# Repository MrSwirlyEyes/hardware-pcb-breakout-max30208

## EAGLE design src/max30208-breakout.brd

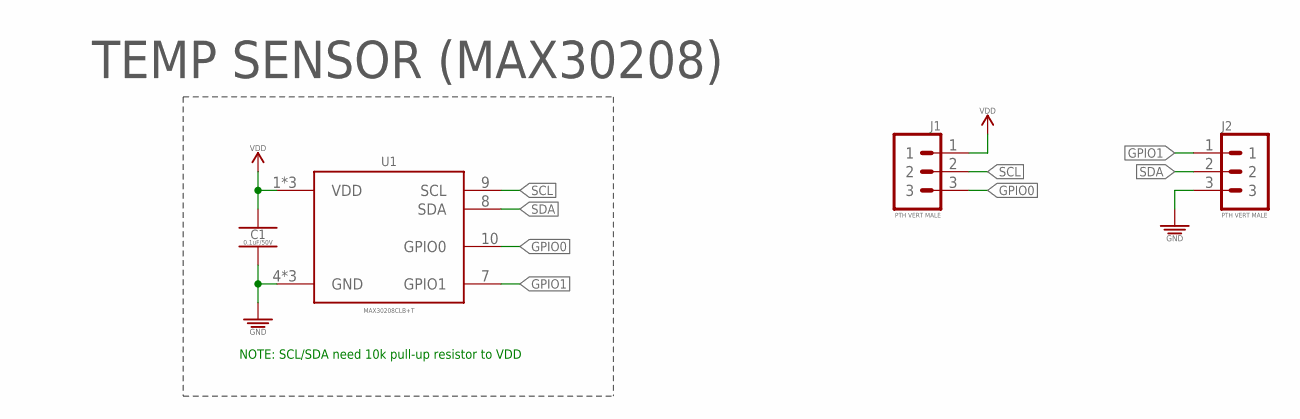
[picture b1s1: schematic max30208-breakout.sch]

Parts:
C1: 0.1uF/50V; CAPC1005X55_SMD-0402
J1, J2: PTH VERT MALE; HDRV3W64P254_1X3_762X254X838B
U1: MAX30208CLB+T; SON65P200X200X85-6N

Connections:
GND: C1.2, J2.3, U1.4 (GND), U1.5 (GND), U1.6 (GND)
GPIO0: J1.3, U1.10 (GPIO0)
GPIO1: J2.1, U1.7 (GPIO1)
SCL: J1.2, U1.9 (SCL)
SDA: J2.2, U1.8 (SDA)
VDD: C1.1, J1.1, U1.1 (VDD), U1.2 (VDD), U1.3 (VDD)

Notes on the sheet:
TEMP SENSOR (MAX30208)
NOTE: SCL/SDA need 10k pull-up resistor to VDD

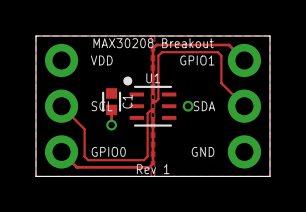
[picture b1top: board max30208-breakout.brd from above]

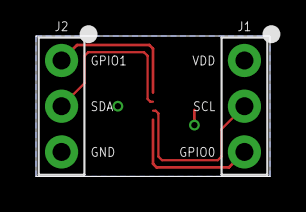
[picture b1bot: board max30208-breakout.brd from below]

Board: 2 copper layers, 13.0 x 7.8 mm, 4 parts (2 on the bottom side), 6 nets.

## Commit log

2021-01-12 [Rev 1] - Initialize repo.
2021-08-11 Update CAM files.
